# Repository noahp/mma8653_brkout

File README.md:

mma8653_brkout
=====

Breakout for freescale MMA8653FC

pcb renders
=====

sch
=====
https://github.com/noahp/mma8653_brkout/raw/master/mma8652_brkout.pdf

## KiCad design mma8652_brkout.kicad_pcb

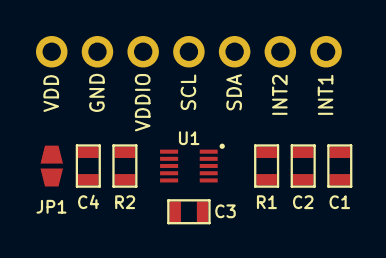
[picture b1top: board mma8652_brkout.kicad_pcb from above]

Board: 2 copper layers, 15 parts (0 on the bottom side), 8 nets, no tracks yet.

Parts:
C1: 1uF; SM0603
C2, C4: 0.1uF; SM0603
C3: 100nF; SM0603
JP1: JUMPER; jmp_small
P1: VDD; TEST_0.100
P2: GND; TEST_0.100
P3: VDDIO; TEST_0.100
P4: SCL; TEST_0.100
P5: SDA; TEST_0.100
P6: INT1; TEST_0.100
P7: INT2; TEST_0.100
R1, R2: 1K; SM0603
U1: MMA8652; mma8652

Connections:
GND: C1.2, C2.2, C3.2, C4.2, P2.1, U1.6, U1.7, U1.9
INT1: P6.1, U1.3
INT2: P7.1, U1.5
unnamed: C3.1, U1.4
SCL: P4.1, R1.1, U1.2
SDA: P5.1, R2.2, U1.10
VDD: C1.1, C2.1, JP1.1, P1.1, U1.1
VDDIO: C4.1, JP1.2, P3.1, R1.2, R2.1, U1.8

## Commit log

2014-01-16 - add submodule kicadlib
2014-01-16 - add project files
2014-01-16 - move mma8652 to kicadlib.
2014-01-16 - add mma8652 footprint
2014-01-17 - start pcb
2014-01-17 - more pcb
2014-01-17 - save pcb. should be rev 0.1
2014-01-17 - add renders
2014-01-22 - add python script for use with bp
2014-01-25 - rename
